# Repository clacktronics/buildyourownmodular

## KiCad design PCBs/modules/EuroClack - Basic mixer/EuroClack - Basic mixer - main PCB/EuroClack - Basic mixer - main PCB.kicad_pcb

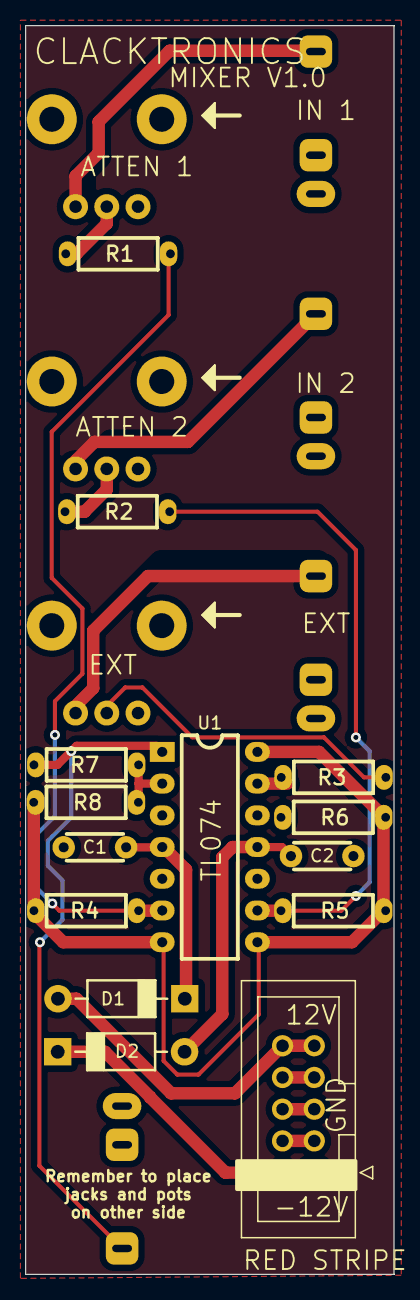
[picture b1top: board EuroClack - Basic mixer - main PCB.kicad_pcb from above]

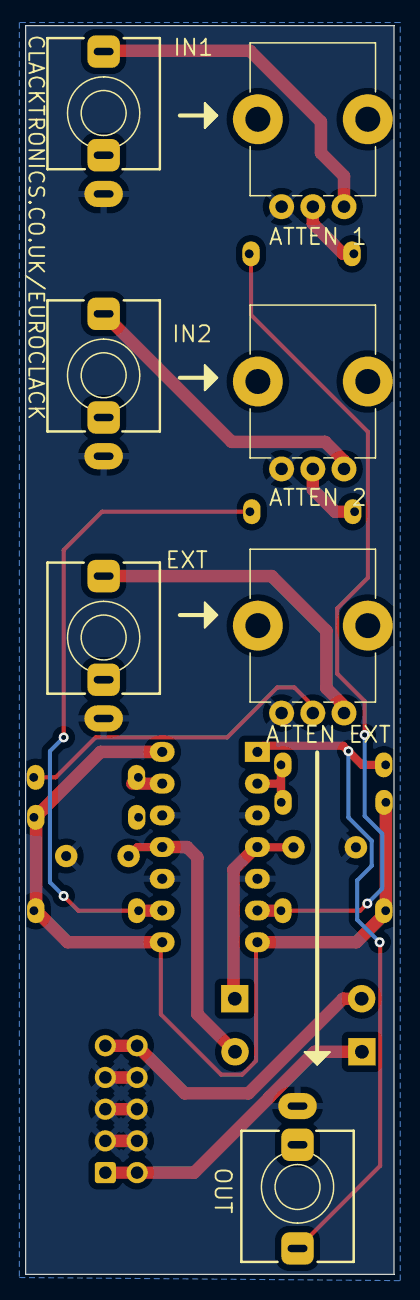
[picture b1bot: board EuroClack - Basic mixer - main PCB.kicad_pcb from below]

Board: 2 copper layers, 29.5 x 100.0 mm, 21 parts (7 on the bottom side), 17 nets.

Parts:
C1, C2: 100n; C_TH_Disc_P5.00mm
D1, D2: D_Schottky; D_TH_DO-41_P10.16mm
J1: input1; Jack_3.5mm_QingPu_WQP-PJ366ST_Vertical
J2: input2; Jack_3.5mm_QingPu_WQP-PJ366ST_Vertical
J3: External; Jack_3.5mm_QingPu_WQP-PJ366ST_Vertical
J4: Output; Jack_3.5mm_QingPu_WQP-PJ366ST_Vertical
J5: Eurorack socket; IDC-Header_2x05_P2.54mm_Vertical
R1, R2, R4, R5, R6, R7, R8: 100k; R_Axial_DIN0204_L3.6mm_D1.6mm_P7.62mm_Horizontal
R3: 47k; R_Axial_DIN0204_L3.6mm_D1.6mm_P7.62mm_Horizontal
RV1, RV2, RV3: 10k; POT_TH_Alps_RK09K_Single_Vertical
U1: TL074; DIP-14_W7.62mm_LongPads

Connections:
+12V: C1.1, D1.1 (K), U1.4 (V+)
-12V: C2.2, D2.2 (A), U1.11 (V-)
GND: C1.2, C2.1, J1.S, J2.S, J3.S, J4.S, J5.3, J5.4, J5.5, J5.6, J5.7, J5.8, RV1.3, RV2.3, RV3.3, U1.3 (+), U1.5 (+), U1.10 (+), U1.12 (+)
unnamed: D1.2 (A), J5.9, J5.10
unnamed: D2.1 (K), J5.1, J5.2
unnamed: J1.T, RV1.1
unnamed: J2.T, RV2.1
unnamed: J3.T, RV3.1
unnamed: J4.T, R7.2, U1.1
unnamed: R1.1, RV1.2
unnamed: R2.1, RV2.2
unnamed: R3.1, RV3.2
unnamed: R4.2, R5.2, R6.2, R8.1, U1.7, U1.8, U1.14
unnamed: R7.1, R8.2, U1.2 (-)
unnamed: R1.2, R4.1, U1.6 (-)
unnamed: R2.2, R5.1, U1.9 (-)
unnamed: R3.2, R6.1, U1.13 (-)

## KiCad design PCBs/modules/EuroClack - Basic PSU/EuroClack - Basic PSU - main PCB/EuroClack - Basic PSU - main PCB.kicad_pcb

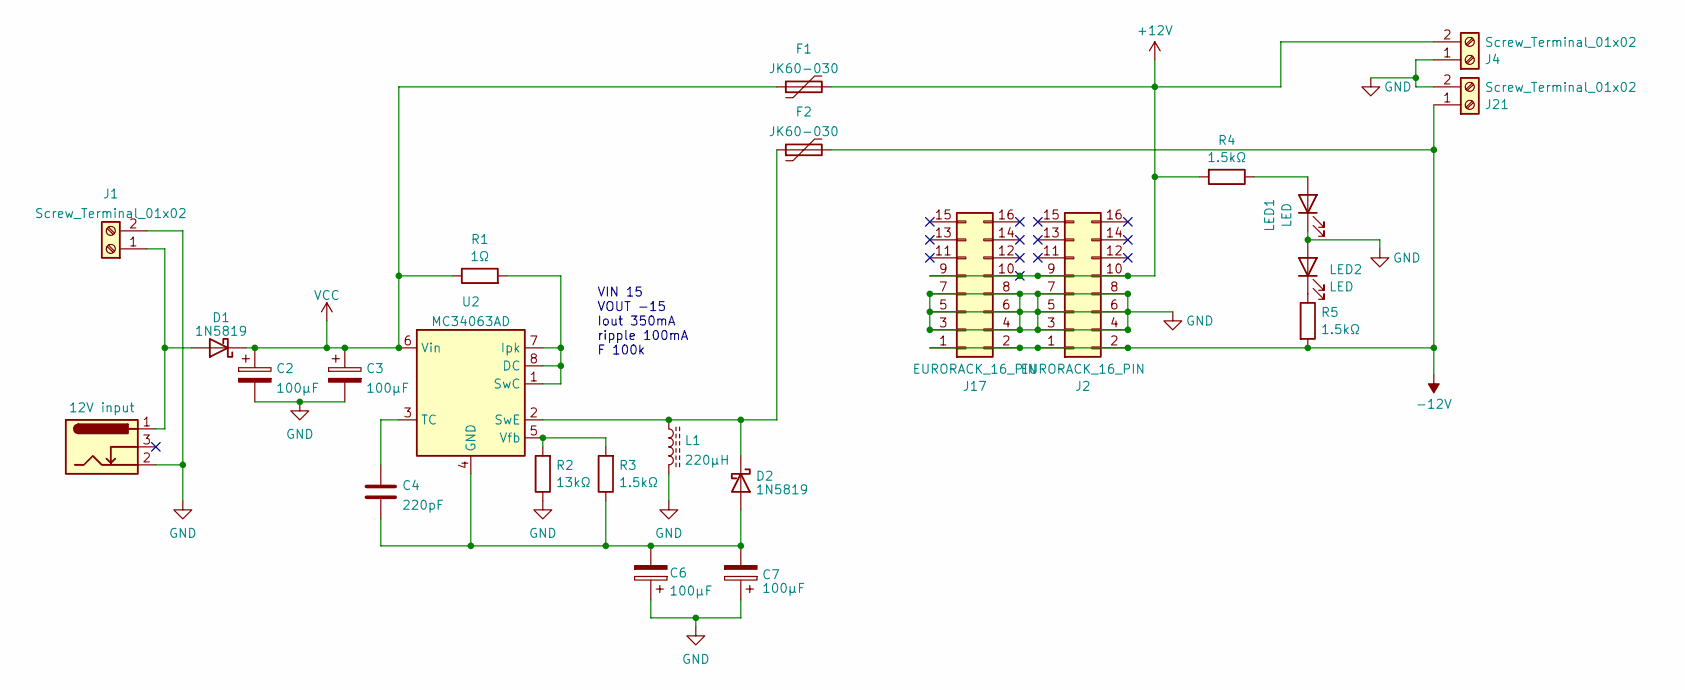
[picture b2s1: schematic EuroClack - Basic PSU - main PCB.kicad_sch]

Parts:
C2, C3, C6, C7: 100μF; C_TH_Elec_5mm_P2mm
C4: 220pF; C_TH_Disc_P5.00mm
D1, D2: 1N5819; D_TH_DO-41_P10.16mm
F1, F2: JK60-030; C_TH_Disc_P5.00mm
J1, J4, J21: Screw_Terminal_01x02; CONN-TH_2P-P3.81_DB125-3.81-2P-BK-S
J2, J17: EURORACK_16_PIN; Eurorack-IDC-Header
J3: 12V input; DC-IN-TH_DC-012A-20A
L1: 220μH; L_Radial_D10.0mm_P5.00mm_Neosid_SD12_style3
LED1, LED2: LED; LED_D3.0mm
R1: 1Ω; R_TH_Axial_250mw_P10.16mm_Horizontal
R2: 13kΩ; R_TH_Axial_250mw_P10.16mm_Horizontal
R3, R4, R5: 1.5kΩ; R_TH_Axial_250mw_P10.16mm_Horizontal
U2: MC34063AD; DIP-8_W7.62mm_LongPads

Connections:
+12V: F1.2, J2.9, J2.10, J4.2, J17.9, J17.10, R4.2
-12V: F2.2, J2.1, J2.2, J17.1, J17.2, J21.1, R5.2
GND: C2.2, C3.2, C6.1, C7.1, J1.2, J2.3, J2.4, J2.5, J2.6, J2.7, J2.8, J3.2, J4.1, J17.3, J17.4, J17.5, J17.6, J17.7, J17.8, J21.2, L1.2, LED1.1 (K), LED2.2 (A), R2.1
unnamed: D1.2 (A), J1.1, J3.1
unnamed: C4.2, C6.2, C7.2, D2.2 (A), R3.1, U2.4 (GND)
unnamed: D2.1 (K), F2.1, L1.1, U2.2 (SwE)
unnamed: LED1.2 (A), R4.1
unnamed: LED2.1 (K), R5.1
unnamed: R1.2, U2.1 (SwC), U2.7 (Ipk), U2.8 (DC)
unnamed: C4.1, U2.3 (TC)
unnamed: R2.2, R3.2, U2.5 (Vfb)
VCC: C2.1, C3.1, D1.1 (K), F1.1, R1.1, U2.6 (Vin)

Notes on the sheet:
VIN 15 VOUT -15 Iout 350mA ripple 100mA F 100k

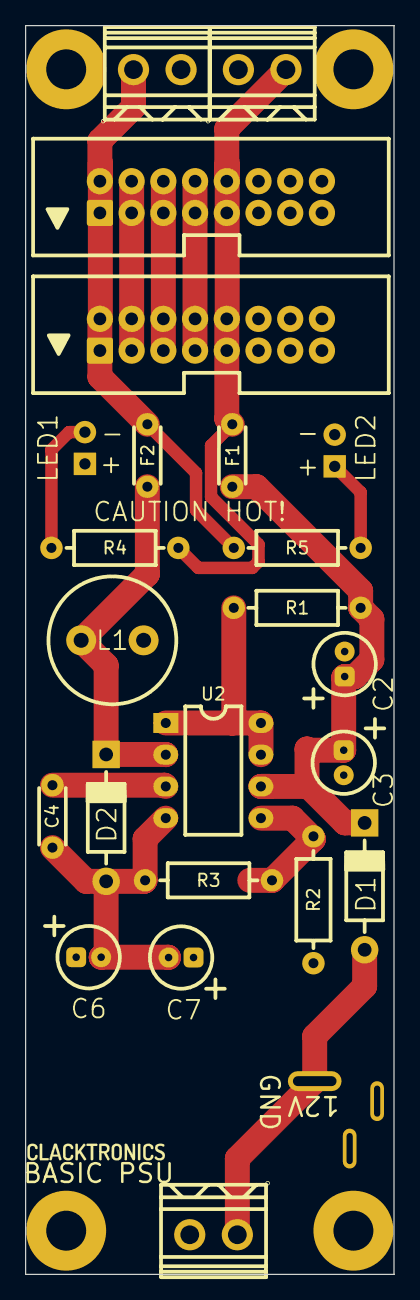
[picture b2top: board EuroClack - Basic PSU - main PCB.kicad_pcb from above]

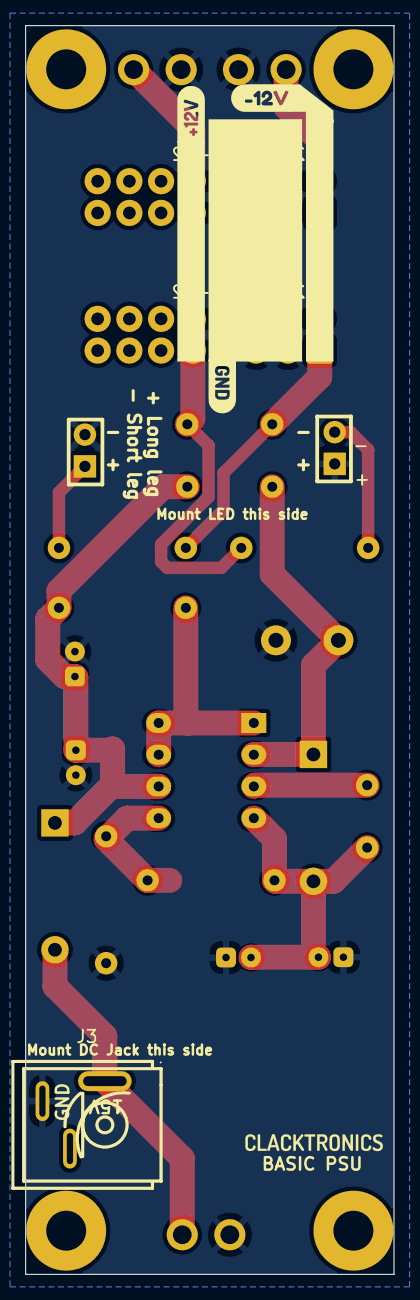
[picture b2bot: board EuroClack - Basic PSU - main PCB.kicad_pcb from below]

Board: 2 copper layers, 29.5 x 100.0 mm, 27 parts (4 on the bottom side), 12 nets.

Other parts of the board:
kibuzzard-63C1369E: G***; kibuzzard-63C1369E
kibuzzard-63C13629: G***; kibuzzard-63C13629
kibuzzard-6399AAFB: G***; kibuzzard-6399AAFB

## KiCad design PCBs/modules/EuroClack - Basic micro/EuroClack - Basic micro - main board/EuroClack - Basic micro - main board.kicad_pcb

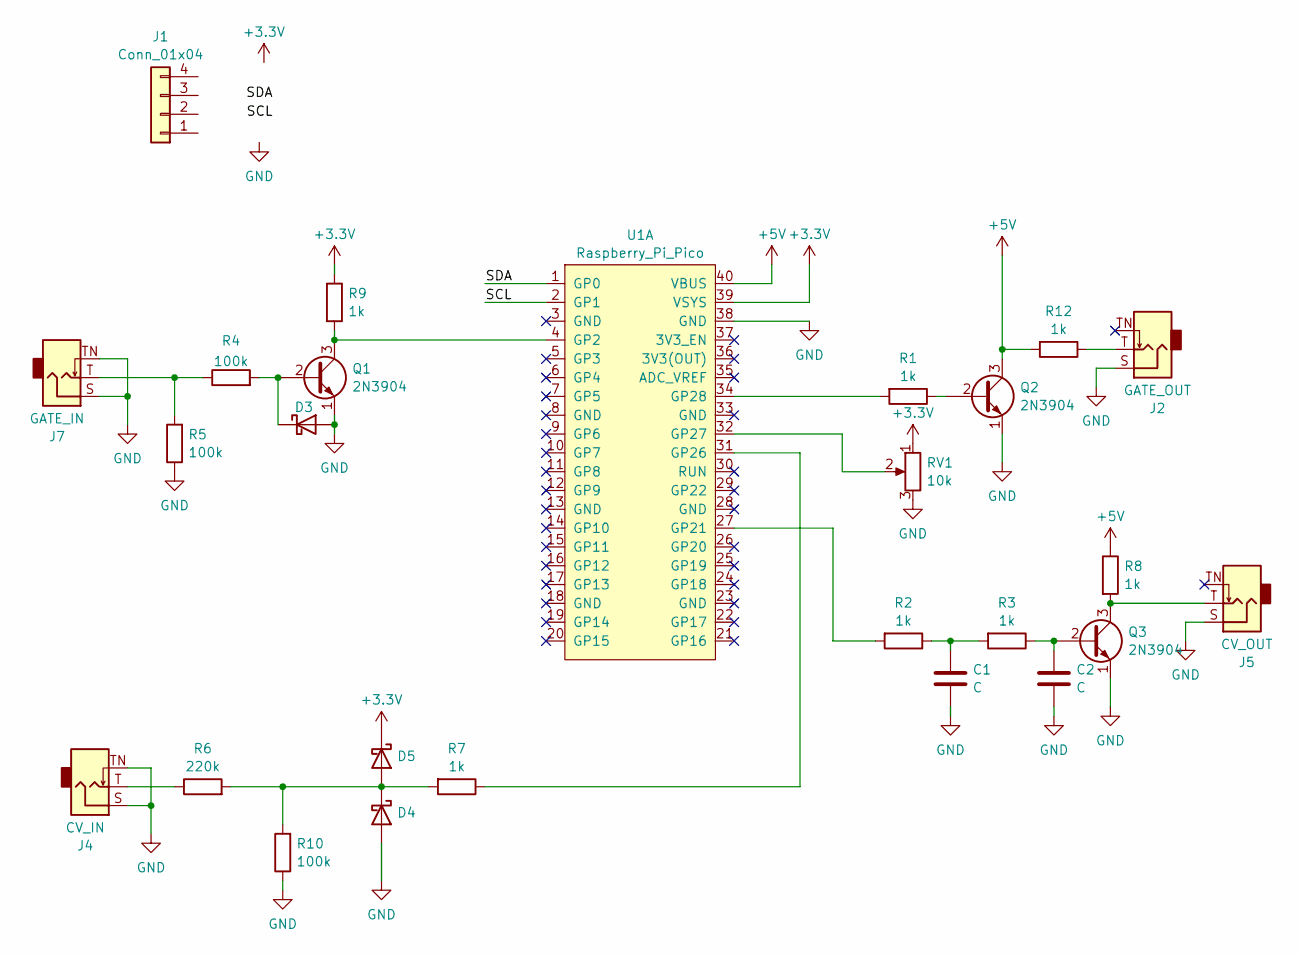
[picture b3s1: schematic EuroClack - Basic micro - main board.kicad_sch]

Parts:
C1, C2: C; C_TH_Disc_P5.00mm
D3, D4, D5: 1N5819WS; D_TH_DO-41_P10.16mm
J1: Conn_01x04
J2: GATE_OUT; Jack_3.5mm_QingPu_WQP-PJ398SM_Vertical
J4: CV_IN; Jack_3.5mm_QingPu_WQP-PJ398SM_Vertical
J5: CV_OUT; Jack_3.5mm_QingPu_WQP-PJ398SM_Vertical
J7: GATE_IN; Jack_3.5mm_QingPu_WQP-PJ398SM_Vertical
Q1, Q2, Q3: 2N3904; TO-92_HandSolder
R1, R2, R3, R7, R8, R9, R12: 1k; R_Axial_DIN0204_L3.6mm_D1.6mm_P7.62mm_Horizontal
R4, R5, R10: 100k; R_Axial_DIN0204_L3.6mm_D1.6mm_P7.62mm_Horizontal
R6: 220k; R_Axial_DIN0204_L3.6mm_D1.6mm_P7.62mm_Horizontal
RV1: 10k; POT_TH_Alps_RK09K_Single_Vertical
U1: Raspberry_Pi_Pico; RPI_Pico_through_hole

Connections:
+3.3V: D5.1 (K), R9.1, RV1.1, U1.39 (VSYS)
+5V: Q2.3 (C), R8.1, R12.2, U1.40 (VBUS)
/SCL: U1.2 (GP1)
/SDA: U1.1 (GP0)
GND: C1.2, C2.2, D3.2 (A), D4.2 (A), J2.S, J4.S, J4.TN, J5.S, J7.S, J7.TN, Q1.1 (E), Q2.1 (E), Q3.1 (E), R5.1, R10.1, RV1.3, U1.38 (GND)
unnamed: C1.1, R2.1, R3.2
unnamed: D3.1 (K), Q1.2 (B), R4.2
unnamed: D4.1 (K), D5.2 (A), R6.2, R7.2, R10.2
unnamed: J2.T, R12.1
unnamed: J4.T, R6.1
unnamed: J7.T, R4.1, R5.2
unnamed: Q1.3 (C), R9.2, U1.4 (GP2)
unnamed: Q2.2 (B), R1.1
unnamed: C2.1, Q3.2 (B), R3.1
unnamed: J5.T, Q3.3 (C), R8.2
unnamed: R2.2, U1.27 (GP21)
unnamed: R7.1, U1.31 (GP26)
unnamed: RV1.2, U1.32 (GP27)
unnamed: R1.2, U1.34 (GP28)

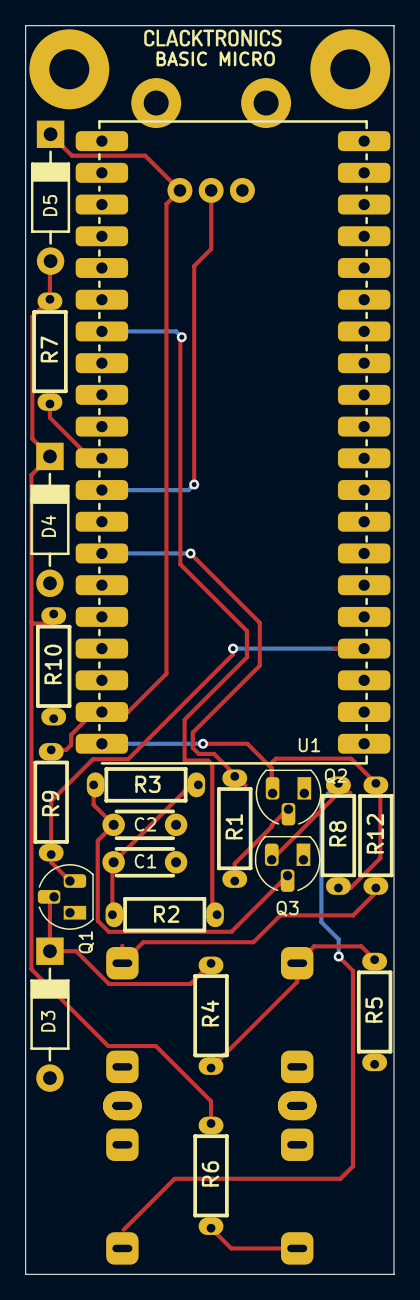
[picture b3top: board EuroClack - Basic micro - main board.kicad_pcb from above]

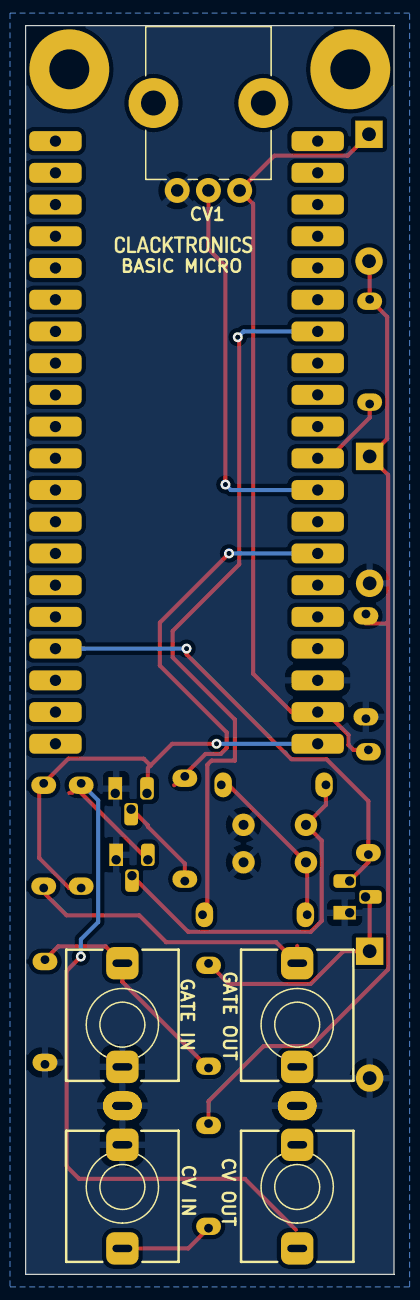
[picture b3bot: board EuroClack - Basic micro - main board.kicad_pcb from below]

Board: 2 copper layers, 29.5 x 100.0 mm, 25 parts (5 on the bottom side), 17 nets.

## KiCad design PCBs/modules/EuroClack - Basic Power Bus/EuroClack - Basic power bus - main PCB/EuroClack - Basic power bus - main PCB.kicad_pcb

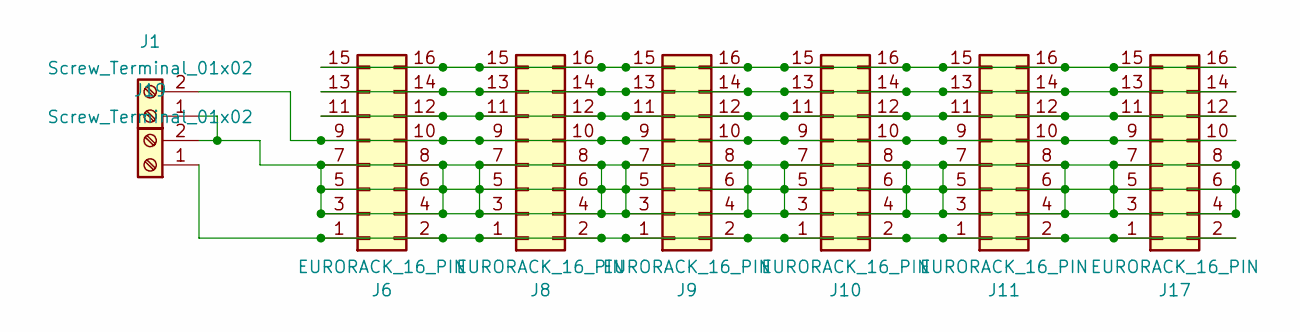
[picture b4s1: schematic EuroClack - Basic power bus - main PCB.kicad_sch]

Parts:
J1, J19: Screw_Terminal_01x02; CONN-TH_2P-P3.81_DB125-3.81-2P-BK-S
J6, J8, J9, J10, J11, J17: EURORACK_16_PIN; Eurorack_16_header

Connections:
unnamed: J1.1, J6.3, J6.4, J6.5, J6.6, J6.7, J6.8, J8.3, J8.4, J8.5, J8.6, J8.7, J8.8, J9.3, J9.4, J9.5, J9.6, J9.7, J9.8, J10.3, J10.4, J10.5, J10.6, J10.7, J10.8, J11.3, J11.4, J11.5, J11.6, J11.7, J11.8, J17.3, J17.4, J17.5, J17.6, J17.7, J17.8, J19.2
unnamed: J1.2, J6.9, J6.10, J8.9, J8.10, J9.9, J9.10, J10.9, J10.10, J11.9, J11.10, J17.9, J17.10
unnamed: J6.1, J6.2, J8.1, J8.2, J9.1, J9.2, J10.1, J10.2, J11.1, J11.2, J17.1, J17.2, J19.1
unnamed: J6.11, J6.12, J8.11, J8.12, J9.11, J9.12, J10.11, J10.12, J11.11, J11.12, J17.11, J17.12
unnamed: J6.13, J6.14, J8.13, J8.14, J9.13, J9.14, J10.13, J10.14, J11.13, J11.14, J17.13, J17.14
unnamed: J6.15, J6.16, J8.15, J8.16, J9.15, J9.16, J10.15, J10.16, J11.15, J11.16, J17.15, J17.16

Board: 2 copper layers, 8 parts (0 on the bottom side), 6 nets, no tracks yet.

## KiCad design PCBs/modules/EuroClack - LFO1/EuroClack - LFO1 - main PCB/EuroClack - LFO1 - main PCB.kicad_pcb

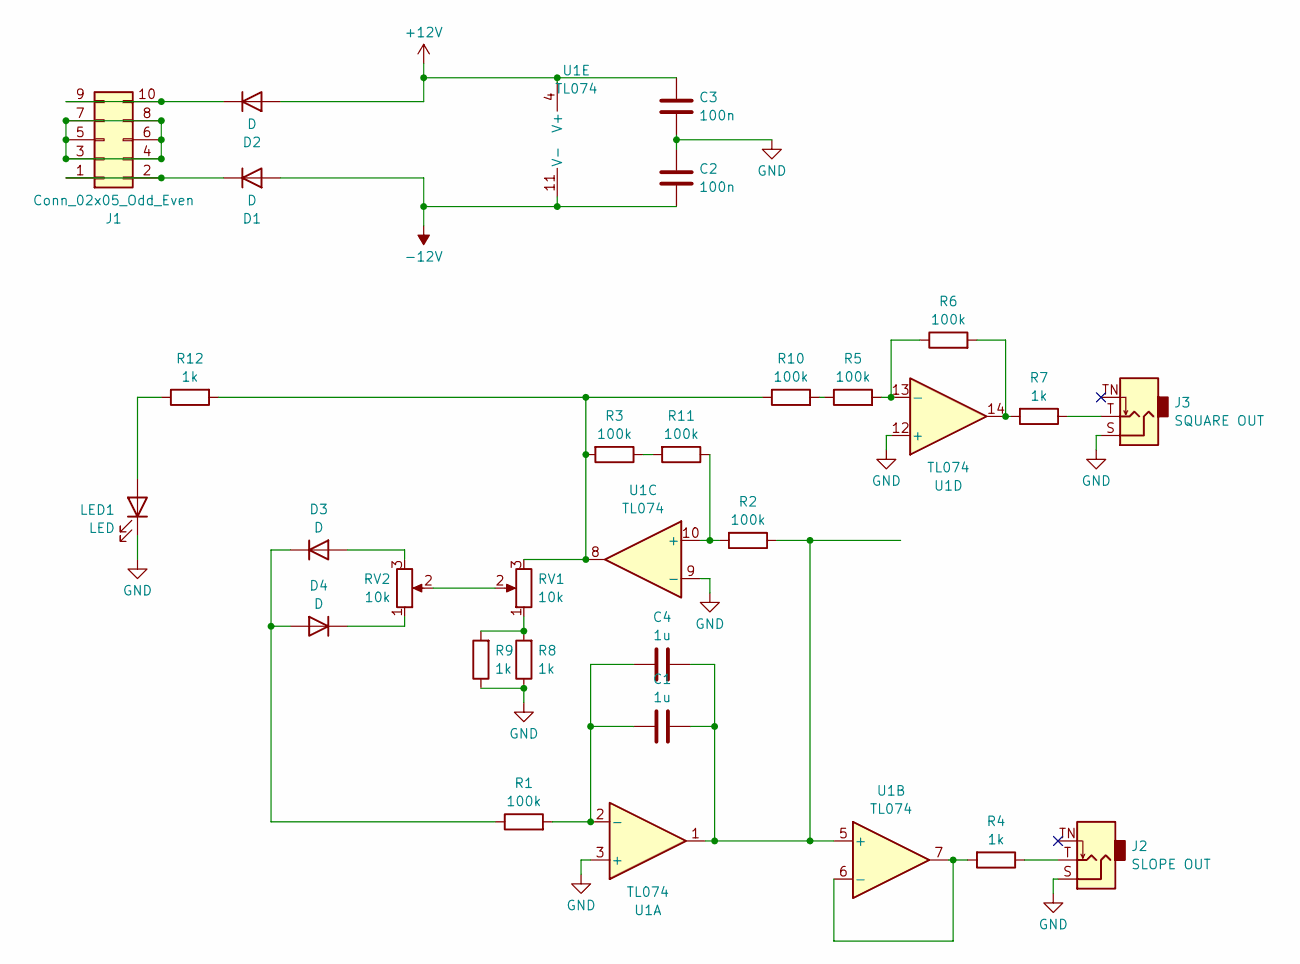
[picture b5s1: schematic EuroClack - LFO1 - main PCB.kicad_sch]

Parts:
C1, C4: 1u; C_TH_Disc_P5.00mm
C2, C3: 100n; C_TH_Disc_P5.00mm
D1, D2, D3, D4: D; D_TH_DO-41_P10.16mm
J1: Conn_02x05_Odd_Even; IDC-Header_2x05_P2.54mm_Vertical
J2: SLOPE OUT; Jack_3.5mm_QingPu_WQP-PJ366ST_Vertical
J3: SQUARE OUT; Jack_3.5mm_QingPu_WQP-PJ366ST_Vertical
LED1: LED; LED_D3.0mm
R1, R2, R3, R5, R6, R10, R11: 100k; R_Axial_DIN0204_L3.6mm_D1.6mm_P7.62mm_Horizontal
R4, R7, R8, R9, R12: 1k; R_Axial_DIN0204_L3.6mm_D1.6mm_P7.62mm_Horizontal
RV1, RV2: 10k; POT_TH_Alps_RK09K_Single_Vertical
U1: TL074; DIP-14_W7.62mm_LongPads

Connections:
+12V: C3.2, D2.2 (A), U1.4 (V+)
-12V: C2.1, D1.2 (A), U1.11 (V-)
GND: C2.2, C3.1, J2.S, J3.S, LED1.1 (K), R8.1, R9.1, U1.3 (+), U1.9 (-), U1.12 (+)
unnamed: D1.1 (K), J1.1, J1.2
unnamed: D2.1 (K), J1.9, J1.10
unnamed: D3.2 (A), RV2.3
unnamed: D3.1 (K), D4.2 (A), R1.1
unnamed: D4.1 (K), RV2.1
unnamed: J1.3, J1.4, J1.5, J1.6, J1.7, J1.8
unnamed: J2.T, R4.1
unnamed: J3.T, R7.1
unnamed: LED1.2 (A), R12.1
unnamed: R6.2, R7.2, U1.14
unnamed: R8.2, R9.2, RV1.1
unnamed: R3.2, R10.1, R12.2, RV1.3, U1.8
unnamed: R5.1, R10.2
unnamed: R3.1, R11.2
unnamed: RV1.2, RV2.2
unnamed: C1.1, C4.1, R1.2, U1.2 (-)
unnamed: C1.2, C4.2, R2.1, U1.1, U1.5 (+)
unnamed: R4.2, U1.6 (-), U1.7
unnamed: R2.2, R11.1, U1.10 (+)
unnamed: R5.2, R6.1, U1.13 (-)

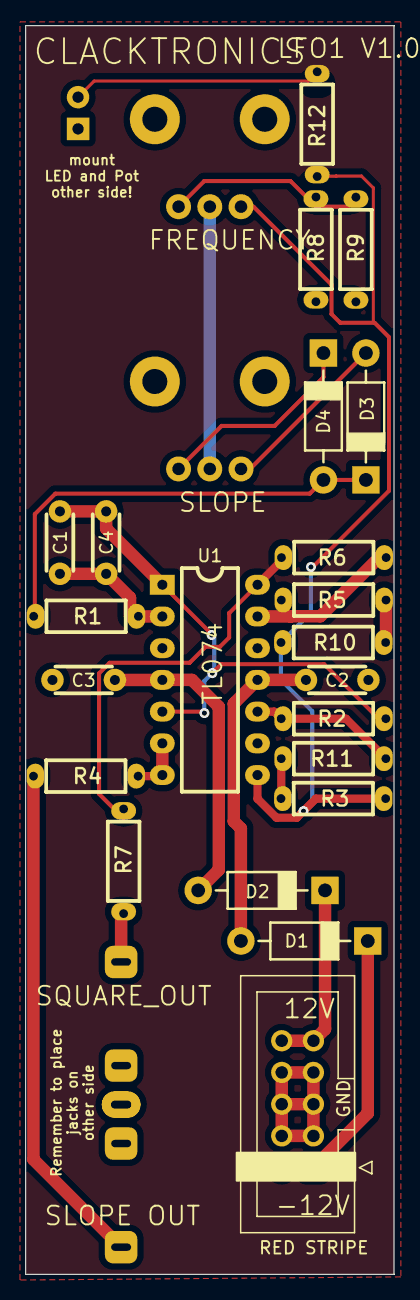
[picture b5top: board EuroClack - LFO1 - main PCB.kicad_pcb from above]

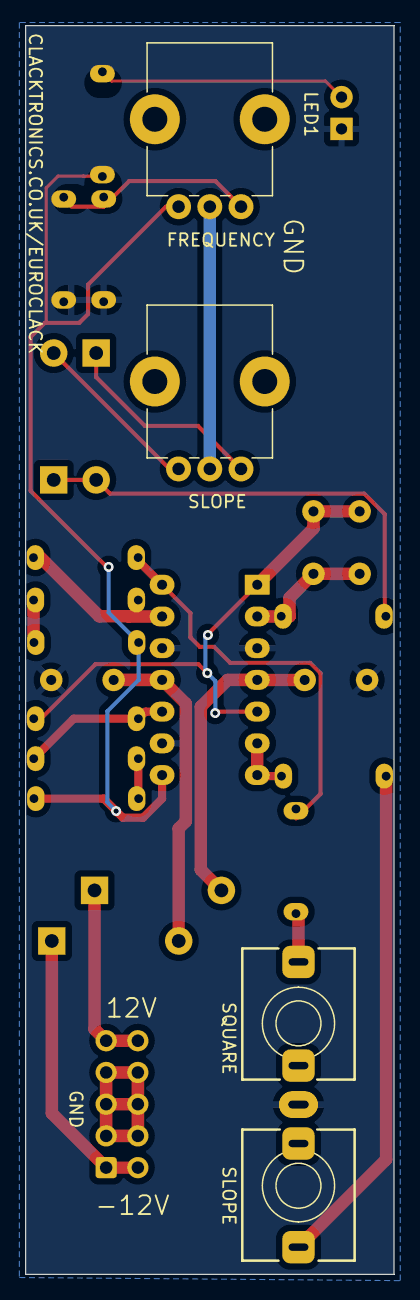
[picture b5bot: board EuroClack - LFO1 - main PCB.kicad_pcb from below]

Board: 2 copper layers, 29.5 x 100.0 mm, 27 parts (5 on the bottom side), 23 nets.

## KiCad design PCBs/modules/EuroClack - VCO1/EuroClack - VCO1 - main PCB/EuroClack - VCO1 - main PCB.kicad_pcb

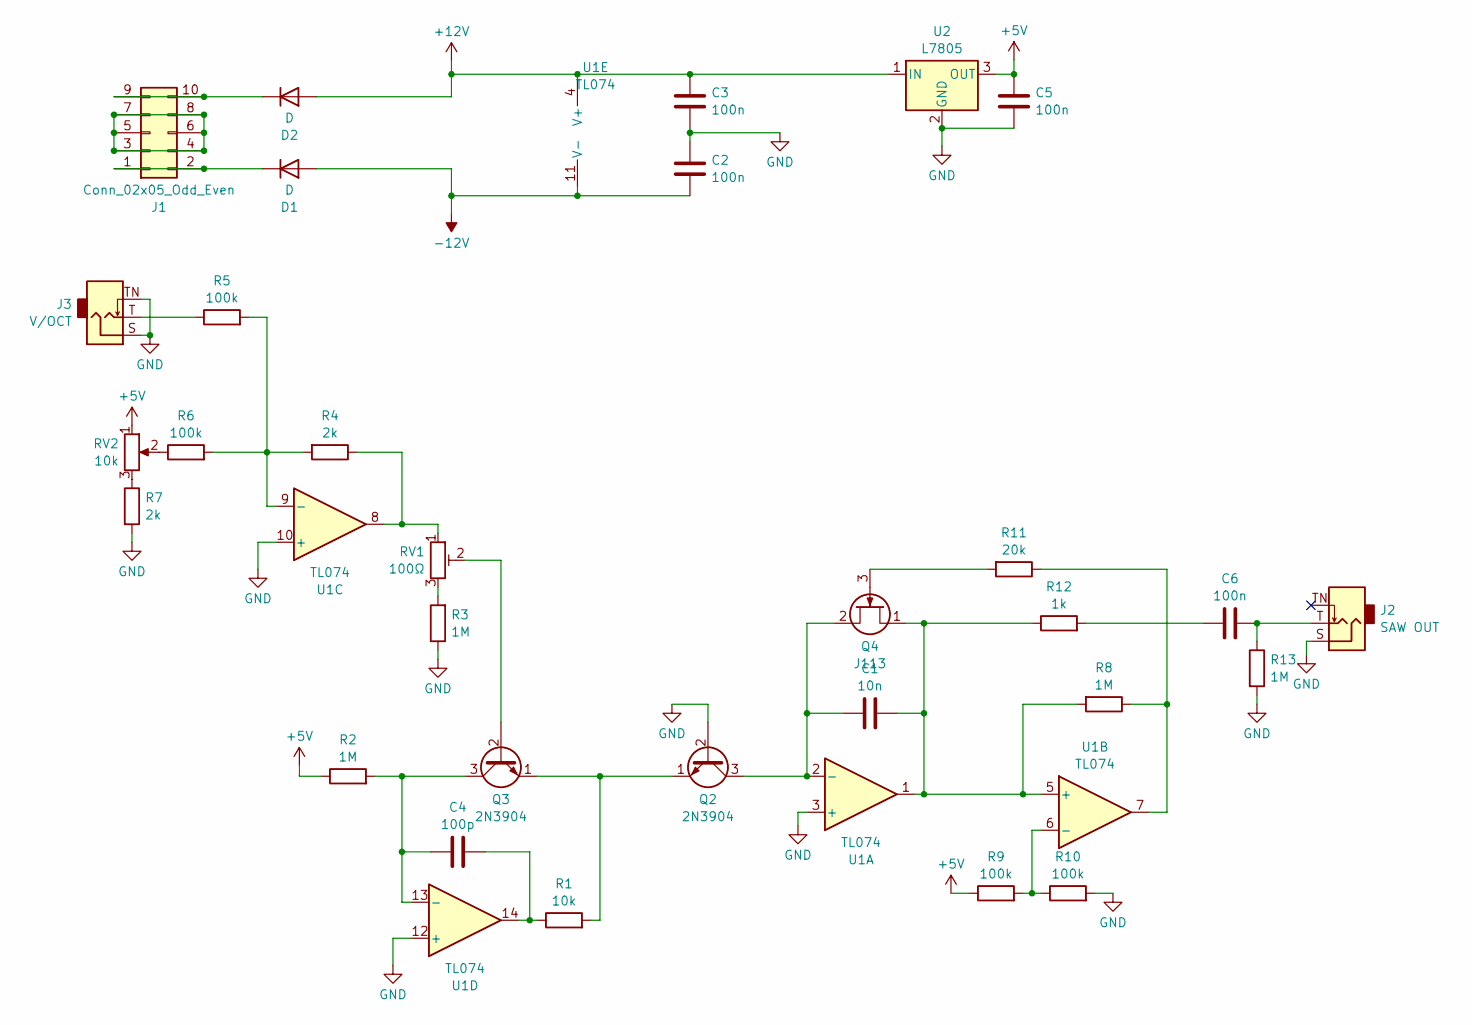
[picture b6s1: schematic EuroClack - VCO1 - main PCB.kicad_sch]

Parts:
C1: 10n; C_TH_Disc_P5.00mm
C2, C3, C5, C6: 100n; C_TH_Disc_P5.00mm
C4: 100p; C_TH_Disc_P5.00mm
D1, D2: D; D_TH_DO-41_P10.16mm
J1: Conn_02x05_Odd_Even; IDC-Header_2x05_P2.54mm_Vertical
J2: SAW OUT; Jack_3.5mm_QingPu_WQP-PJ366ST_Vertical
J3: V/OCT; Jack_3.5mm_QingPu_WQP-PJ366ST_Vertical
Q2, Q3: 2N3904; TO-92_HandSolder
Q4: J113; TO-92L_HandSolder
R1: 10k; R_Axial_DIN0204_L3.6mm_D1.6mm_P7.62mm_Horizontal
R2, R3, R8, R13: 1M; R_Axial_DIN0204_L3.6mm_D1.6mm_P7.62mm_Horizontal
R4, R7: 2k; R_Axial_DIN0204_L3.6mm_D1.6mm_P7.62mm_Horizontal
R5, R6, R9, R10: 100k; R_Axial_DIN0204_L3.6mm_D1.6mm_P7.62mm_Horizontal
R11: 20k; R_Axial_DIN0204_L3.6mm_D1.6mm_P7.62mm_Horizontal
R12: 1k; R_Axial_DIN0204_L3.6mm_D1.6mm_P7.62mm_Horizontal
RV1: 100Ω; Potentiometer_Bourns_3296W_Vertical
RV2: 10k; POT_TH_Alps_RK09K_Single_Vertical
U1: TL074; DIP-14_W7.62mm_LongPads
U2: L7805; TO-92

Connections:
+5V: C5.2, R2.1, R9.1, RV2.1, U2.3 (OUT)
+12V: C3.2, D2.2 (A), U1.4 (V+), U2.1 (IN)
-12V: C2.1, D1.2 (A), U1.11 (V-)
GND: C2.2, C3.1, C5.1, J2.S, J3.S, J3.TN, Q2.2 (B), R3.1, R7.2, R10.2, R13.2, U1.3 (+), U1.10 (+), U1.12 (+), U2.2 (GND)
unnamed: C4.2, R1.1, U1.14
unnamed: C6.1, R12.2
unnamed: C6.2, J2.T, R13.1
unnamed: D1.1 (K), J1.1, J1.2
unnamed: D2.1 (K), J1.9, J1.10
unnamed: J1.3, J1.4, J1.5, J1.6, J1.7, J1.8
unnamed: J3.T, R5.1
unnamed: C1.1, Q2.3 (C), Q4.2 (S), U1.2 (-)
unnamed: Q2.1 (E), Q3.1 (E), R1.2
unnamed: Q3.2 (B), RV1.2
unnamed: C4.1, Q3.3 (C), R2.2, U1.13 (-)
unnamed: C1.2, Q4.1 (D), R8.2, R12.1, U1.1, U1.5 (+)
unnamed: Q4.3 (G), R11.2
unnamed: R3.2, RV1.3
unnamed: R4.1, RV1.1, U1.8
unnamed: R6.1, RV2.2
unnamed: R7.1, RV2.3
unnamed: R8.1, R11.1, U1.7
unnamed: R9.2, R10.1, U1.6 (-)
unnamed: R4.2, R5.2, R6.2, U1.9 (-)

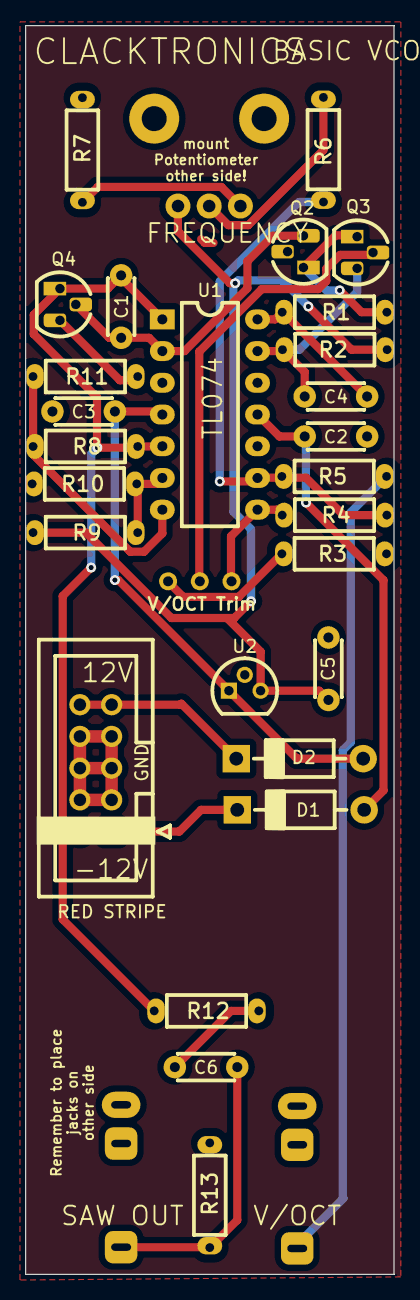
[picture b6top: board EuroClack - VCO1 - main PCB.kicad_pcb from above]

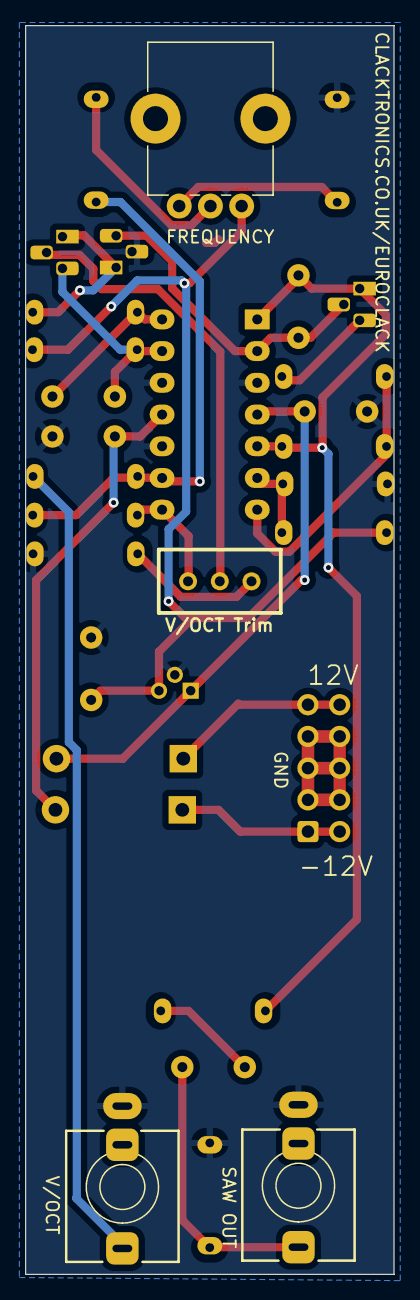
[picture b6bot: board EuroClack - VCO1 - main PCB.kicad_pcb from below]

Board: 2 copper layers, 29.5 x 100.0 mm, 31 parts (4 on the bottom side), 24 nets.

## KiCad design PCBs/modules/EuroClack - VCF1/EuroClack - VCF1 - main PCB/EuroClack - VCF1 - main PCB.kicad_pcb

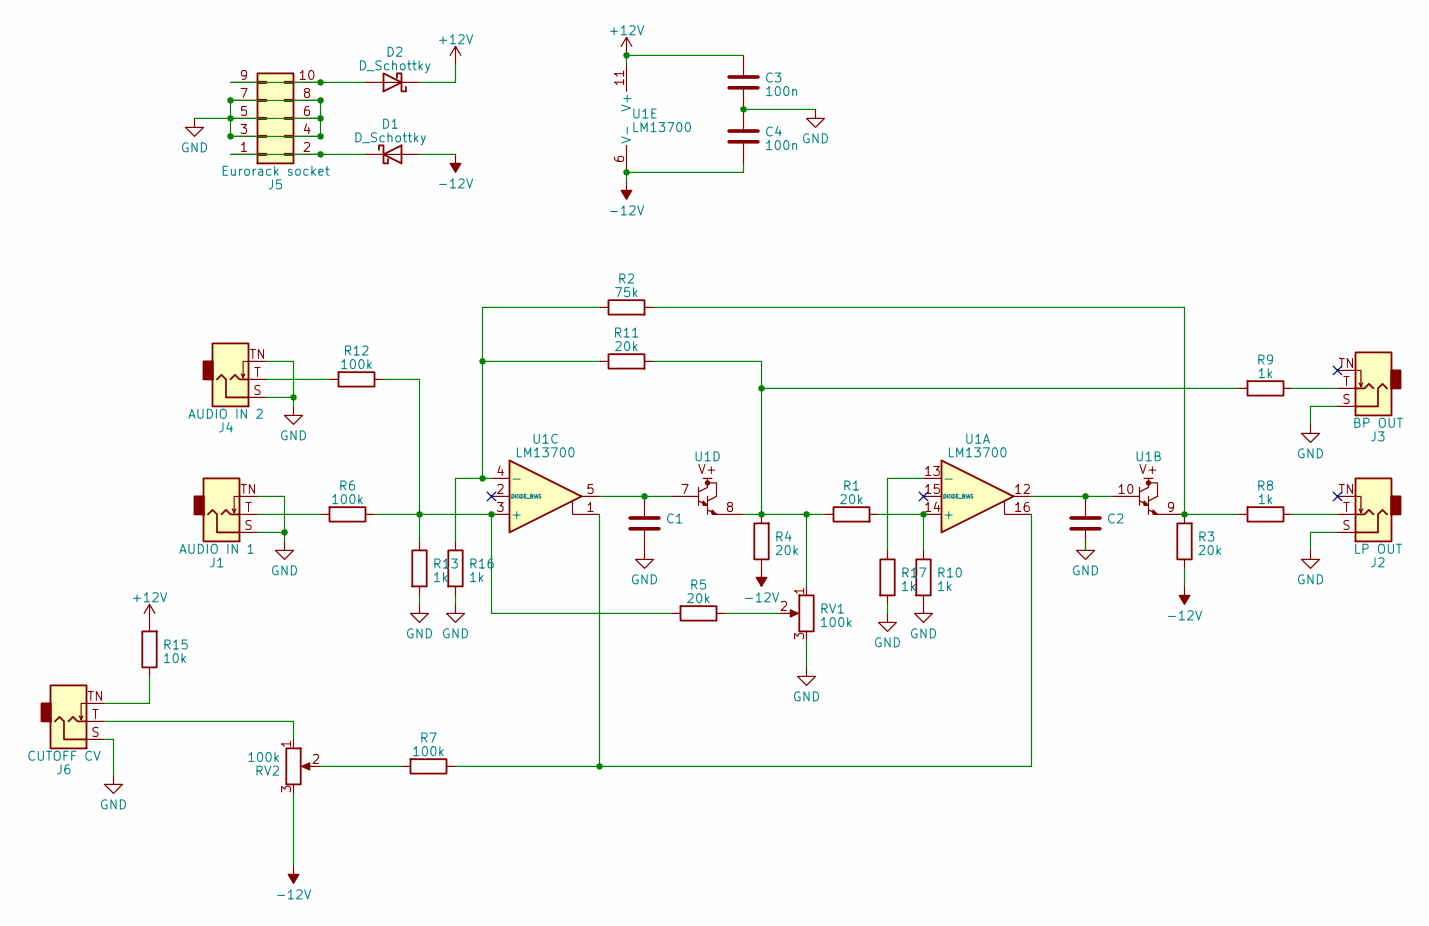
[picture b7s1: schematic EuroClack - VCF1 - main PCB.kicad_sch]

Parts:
C1, C2: C_TH_Disc_P5.00mm
C3, C4: 100n; C_TH_Disc_P5.00mm
D1, D2: D_Schottky; D_TH_DO-41_P10.16mm
J1: AUDIO IN 1; Jack_3.5mm_QingPu_WQP-PJ301M-12_Vertical
J2: LP OUT; Jack_3.5mm_QingPu_WQP-PJ301M-12_Vertical
J3: BP OUT; Jack_3.5mm_QingPu_WQP-PJ301M-12_Vertical
J4: AUDIO IN 2; Jack_3.5mm_QingPu_WQP-PJ301M-12_Vertical
J5: Eurorack socket; IDC-Header_2x05_P2.54mm_Vertical
J6: CUTOFF CV; Jack_3.5mm_QingPu_WQP-PJ301M-12_Vertical
R1, R3, R4, R5, R11: 20k; R_Axial_DIN0204_L3.6mm_D1.6mm_P7.62mm_Horizontal
R2: 75k; R_Axial_DIN0204_L3.6mm_D1.6mm_P7.62mm_Horizontal
R6, R7, R12: 100k; R_Axial_DIN0204_L3.6mm_D1.6mm_P7.62mm_Horizontal
R8, R9, R10, R13, R16, R17: 1k; R_Axial_DIN0204_L3.6mm_D1.6mm_P7.62mm_Horizontal
R15: 10k; R_Axial_DIN0204_L3.6mm_D1.6mm_P7.62mm_Horizontal
RV1, RV2: 100k; POT_TH_Alps_RK09K_Single_Vertical
U1: LM13700; DIP-16_W7.62mm_LongPads

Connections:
+12V: C3.1, D2.1 (K), R15.2, U1.11 (V+)
-12V: C4.2, D1.2 (A), R3.1, R4.1, RV2.3, U1.6 (V-)
GND: C1.2, C2.2, C3.2, C4.1, J1.S, J1.TN, J2.S, J3.S, J4.S, J4.TN, J5.3, J5.4, J5.5, J5.6, J5.7, J5.8, J6.S, R10.2, R13.2, R16.2, R17.2, RV1.3
unnamed: C1.1, U1.5, U1.7
unnamed: C2.1, U1.10, U1.12
unnamed: D1.1 (K), J5.1, J5.2
unnamed: D2.2 (A), J5.9, J5.10
unnamed: J1.T, R6.2
unnamed: J2.T, R8.1
unnamed: J3.T, R9.1
unnamed: J4.T, R12.2
unnamed: J6.T, RV2.1
unnamed: J6.TN, R15.1
unnamed: R1.1, R4.2, R9.2, R11.2, RV1.1, U1.8
unnamed: R2.2, R3.2, R8.2, U1.9
unnamed: R5.1, RV1.2
unnamed: R7.1, U1.1, U1.16
unnamed: R7.2, RV2.2
unnamed: R1.2, R10.1, U1.14 (+)
unnamed: R17.1, U1.13 (-)
unnamed: R5.2, R6.1, R12.1, R13.1, U1.3 (+)
unnamed: R2.1, R11.1, R16.1, U1.4 (-)

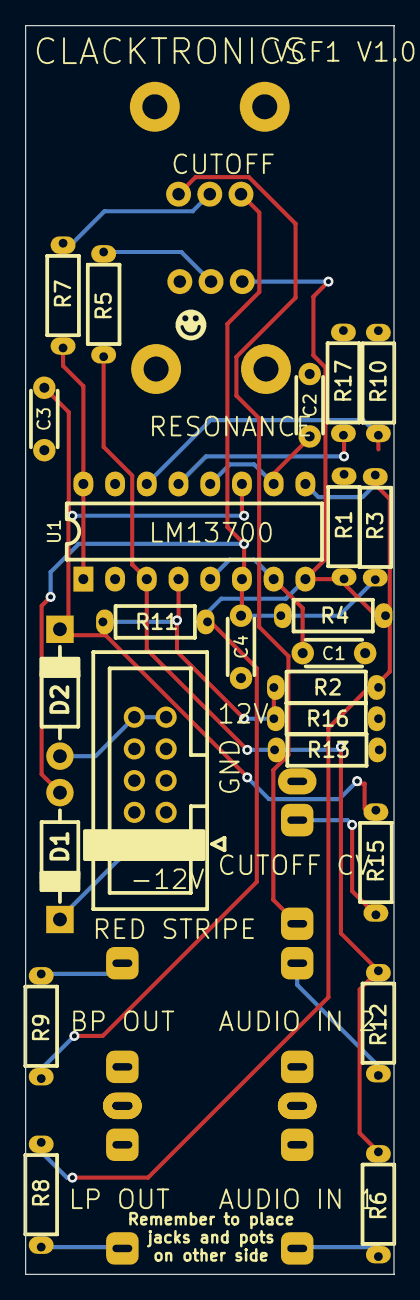
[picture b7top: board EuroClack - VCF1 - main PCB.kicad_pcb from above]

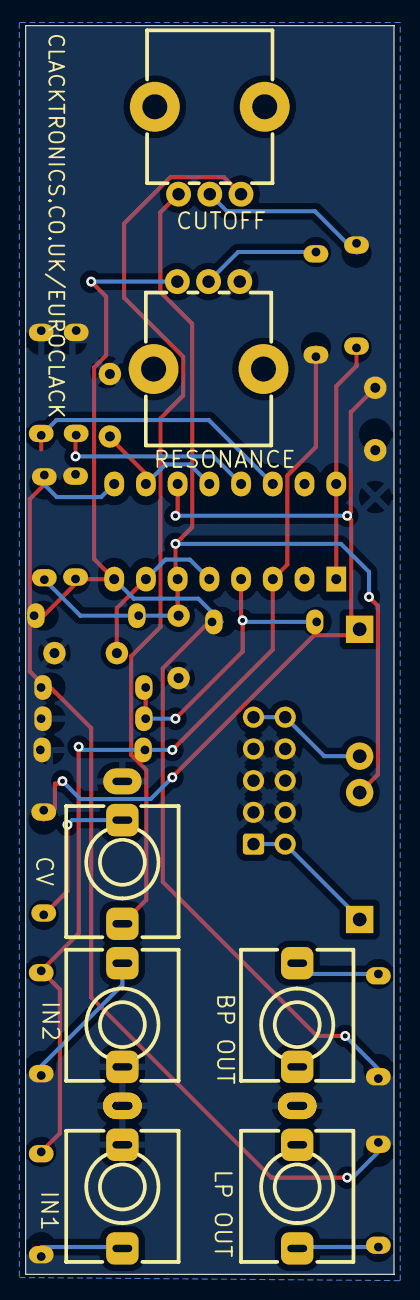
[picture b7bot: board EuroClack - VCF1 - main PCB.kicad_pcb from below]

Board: 2 copper layers, 29.5 x 100.0 mm, 31 parts (7 on the bottom side), 22 nets.

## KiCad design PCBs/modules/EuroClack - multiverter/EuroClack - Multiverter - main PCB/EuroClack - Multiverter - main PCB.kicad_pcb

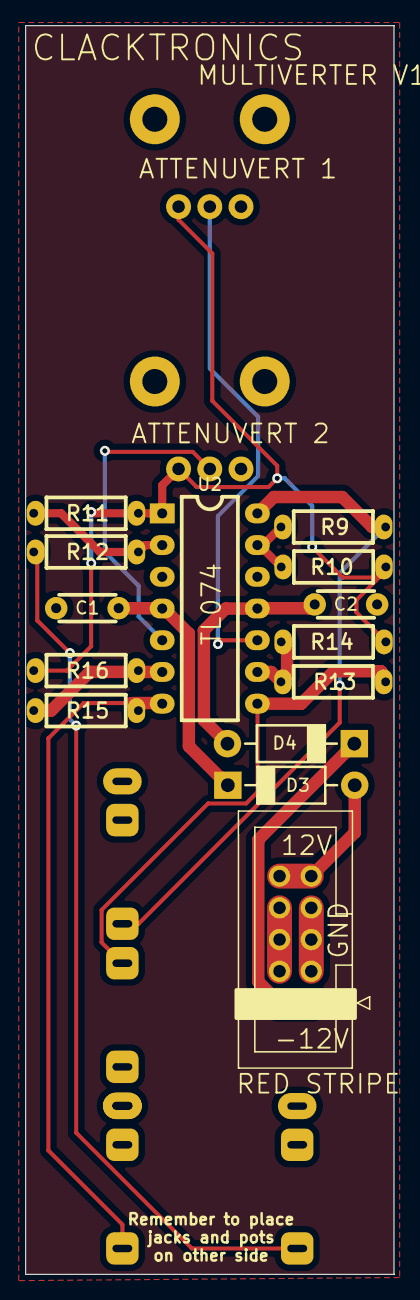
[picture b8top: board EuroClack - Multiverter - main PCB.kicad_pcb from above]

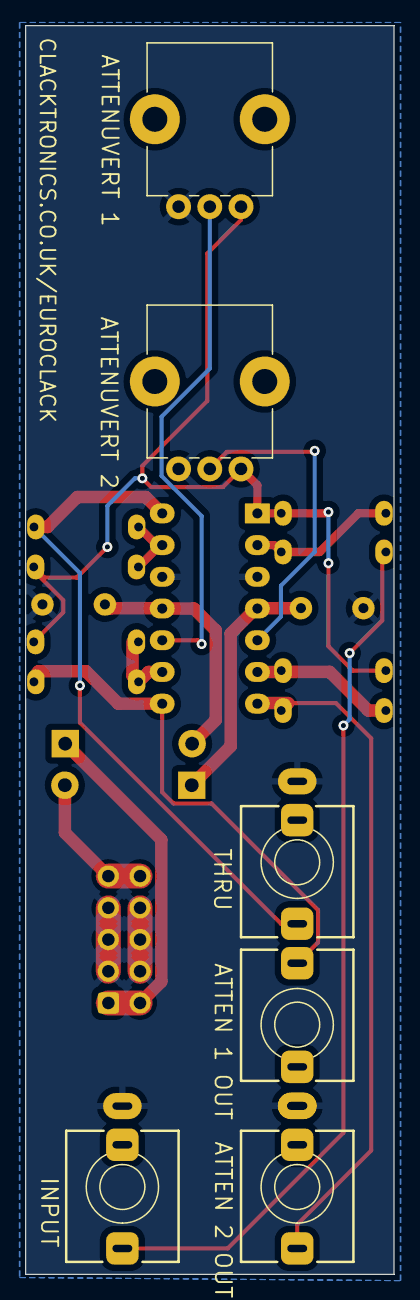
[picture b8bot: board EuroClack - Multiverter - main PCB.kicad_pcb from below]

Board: 2 copper layers, 29.5 x 100.0 mm, 20 parts (6 on the bottom side), 16 nets.

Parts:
C1, C2: 100n; C_TH_Disc_P5.00mm
D3, D4: D_Schottky; D_TH_DO-41_P10.16mm
J6: Eurorack socket; IDC-Header_2x05_P2.54mm_Vertical
J7: Thru; Jack_3.5mm_QingPu_WQP-PJ366ST_Vertical
J8: input; Jack_3.5mm_QingPu_WQP-PJ366ST_Vertical
J9: Attenuvert 1; Jack_3.5mm_QingPu_WQP-PJ366ST_Vertical
J10: Attenuvert 2; Jack_3.5mm_QingPu_WQP-PJ366ST_Vertical
R9, R10, R11, R12, R13, R14, R15, R16: 100k; R_Axial_DIN0204_L3.6mm_D1.6mm_P7.62mm_Horizontal
RV5, RV6: 10k; POT_TH_Alps_RK09K_Single_Vertical
U2: TL074; DIP-14_W7.62mm_LongPads

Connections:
+12V: C1.1, D3.1 (K), U2.4 (V+)
-12V: C2.2, D4.2 (A), U2.11 (V-)
GND: C1.2, C2.1, J6.3, J6.4, J6.5, J6.6, J6.7, J6.8, J7.S, J8.S, J9.S, J10.S, RV5.3, RV6.3, U2.3 (+), U2.12 (+)
unnamed: D3.2 (A), J6.9, J6.10
unnamed: D4.1 (K), J6.1, J6.2
unnamed: J7.T, R9.2, U2.14
unnamed: J8.T, R12.1
unnamed: J9.T, R13.2, U2.8
unnamed: J10.T, R15.2, U2.7
unnamed: R10.1, R11.2, R14.1, R16.1, RV5.1, RV6.1, U2.1
unnamed: R11.1, R12.2, U2.2 (-)
unnamed: RV6.2, U2.5 (+)
unnamed: R15.1, R16.2, U2.6 (-)
unnamed: RV5.2, U2.10 (+)
unnamed: R13.1, R14.2, U2.9 (-)
unnamed: R9.1, R10.2, U2.13 (-)

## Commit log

2023-12-21 init
